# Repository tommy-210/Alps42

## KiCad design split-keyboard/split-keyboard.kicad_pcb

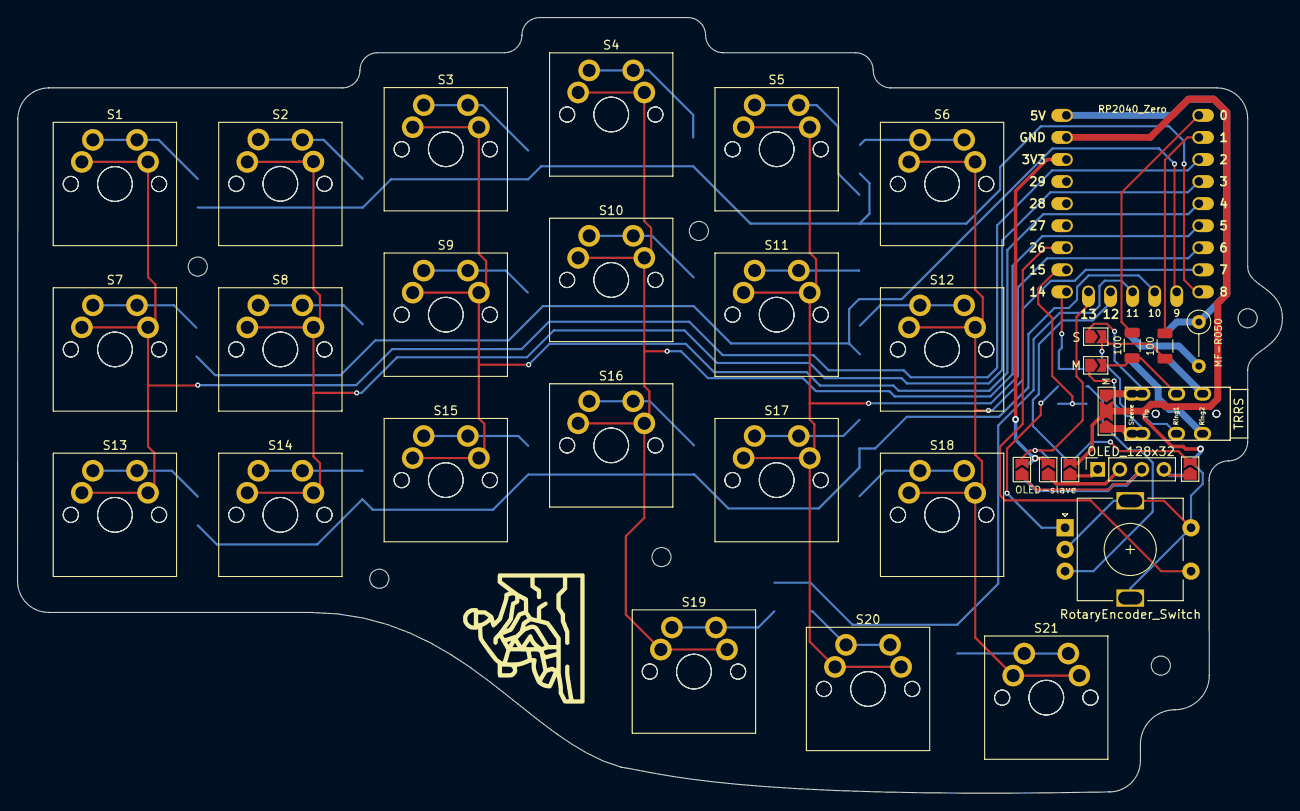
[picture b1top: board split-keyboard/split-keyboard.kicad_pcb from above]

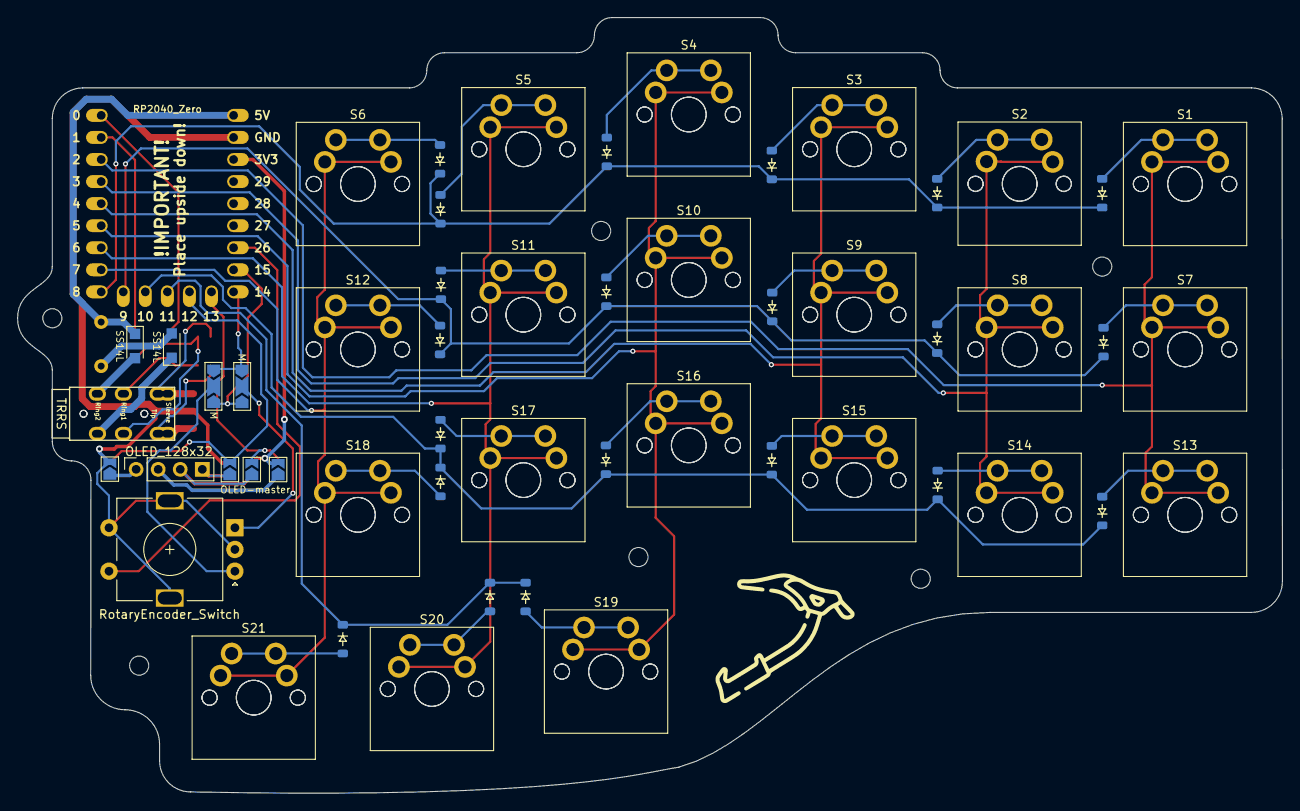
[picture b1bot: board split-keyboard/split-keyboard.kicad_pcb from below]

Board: 2 copper layers, 145.7 x 89.3 mm, 86 parts (51 on the bottom side), 56 nets.

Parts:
D1, D2, D3, D4, D5, D6, D7, D8, D9, D10, D11, D12, D13, D14, D15, D16, D17, D18, D19, D20, D21: Diode_SOD-123
D22, D23: SS14L; Nexperia_CFP3_SOD-123W
F1: MF-R050; R_Axial_DIN0207_L6.3mm_D2.5mm_P5.08mm_Vertical
J1: OLED_128x32; PinSocket_1x04_P2.54mm_Vertical
JP1, JP2, JP3: SolderJumper_3_Open; SolderJumper-3_P2.0mm_Open_TrianglePad1.0x1.5mm_NumberLabels
JP_MGND7: SolderJumper_2_Open; SolderJumper-2_P1.3mm_Open_TrianglePad1.0x1.5mm
JP_MSCL7: SolderJumper_2_Open; SolderJumper-2_P1.3mm_Open_TrianglePad1.0x1.5mm
JP_MSDA6: SolderJumper_2_Open; SolderJumper-2_P1.3mm_Open_TrianglePad1.0x1.5mm
JP_MTX5: SolderJumper_2_Open; SolderJumper-2_P1.3mm_Open_TrianglePad1.0x1.5mm
JP_MVCC8: SolderJumper_2_Open; SolderJumper-2_P1.3mm_Open_TrianglePad1.0x1.5mm
JP_SGND6: SolderJumper_2_Open; SolderJumper-2_P1.3mm_Open_TrianglePad1.0x1.5mm
JP_SRX4: SolderJumper_2_Open; SolderJumper-2_P1.3mm_Open_TrianglePad1.0x1.5mm
JP_SSCL8: SolderJumper_2_Open; SolderJumper-2_P1.3mm_Open_TrianglePad1.0x1.5mm
JP_SSDA5: SolderJumper_2_Open; SolderJumper-2_P1.3mm_Open_TrianglePad1.0x1.5mm
JP_SVCC7: SolderJumper_2_Open; SolderJumper-2_P1.3mm_Open_TrianglePad1.0x1.5mm
R1, R2: 100; R_1206_3216Metric
S1, S1#2, S2, S2#2, S3, S3#2, S4, S4#2, S5, S5#2, S6, S6#2, S7, S7#2, S8, S8#2, S9, S9#2, S10, S10#2, S11, S11#2, S12, S12#2, S13, S13#2, S14, S14#2, S15, S15#2, S16, S16#2, S17, S17#2, S18, S18#2, S19, S19#2, S20, S20#2, S21, S21#2: MX_PCB_1.00u
SW1: RotaryEncoder_Switch; RotaryEncoder_Alps_EC11E-Switch_Vertical_H20mm
U3: RP2040_Zero
U_M1: TRRS; TRRS_PJ-320A
U_S2: TRRS; TRRS_PJ-320A

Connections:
3.3V: JP_MVCC8.2 (B), JP_SVCC7.2 (B), U3.21 (3V3)
5V: D22.1 (K), F1.1, U3.23 (5V)
Column_1: S1.1, S1#2.1, S7.1, S7#2.1, S13.1, S13#2.1, U3.3 (2)
Column_2: S2.1, S2#2.1, S8.1, S8#2.1, S14.1, S14#2.1, U3.4 (3)
Column_3: S3.1, S3#2.1, S9.1, S9#2.1, S15.1, S15#2.1, U3.5 (4)
Column_4: S4.1, S4#2.1, S10.1, S10#2.1, S16.1, S16#2.1, S19.1, S19#2.1, U3.6 (5)
Column_5: S5.1, S5#2.1, S11.1, S11#2.1, S17.1, S17#2.1, S20.1, S20#2.1, U3.7 (6)
Column_6: S6.1, S6#2.1, S12.1, S12#2.1, S18.1, S18#2.1, S21.1, S21#2.1, U3.8 (7)
ENCODER_A: JP1.1 (A), JP2.3 (B), U3.15 (14)
ENCODER_B: JP1.3 (B), JP2.1 (A), U3.16 (15)
ENCODER_SW: SW1.S1, U3.17 (26)
GND: JP3.2 (C), JP_MGND7.2 (B), JP_SGND6.2 (B), SW1.C, SW1.MP, SW1.S2, U3.22 (GND)
unnamed: D1.2 (A), S1.2, S1#2.2
unnamed: D2.2 (A), S2.2, S2#2.2
unnamed: D3.2 (A), S3.2, S3#2.2
unnamed: D4.2 (A), S4.2, S4#2.2
unnamed: D5.2 (A), S5.2, S5#2.2
unnamed: D6.2 (A), S6.2, S6#2.2
unnamed: D7.2 (A), S7.2, S7#2.2
unnamed: D8.2 (A), S8.2, S8#2.2
unnamed: D9.2 (A), S9.2, S9#2.2
unnamed: D10.2 (A), S10.2, S10#2.2
unnamed: D11.2 (A), S11.2, S11#2.2
unnamed: D12.2 (A), S12.2, S12#2.2
unnamed: D13.2 (A), S13.2, S13#2.2
unnamed: D14.2 (A), S14.2, S14#2.2
unnamed: D15.2 (A), S15.2, S15#2.2
unnamed: D16.2 (A), S16.2, S16#2.2
unnamed: D17.2 (A), S17.2, S17#2.2
unnamed: D18.2 (A), S18.2, S18#2.2
unnamed: D19.2 (A), S19.2, S19#2.2
unnamed: D20.2 (A), S20.2, S20#2.2
unnamed: D21.2 (A), S21.2, S21#2.2
unnamed: D22.2 (A), U_S2.4 (RING2)
unnamed: D23.2 (A), F1.2
unnamed: D23.1 (K), U_M1.4 (RING2)
unnamed: J1.1, JP_MSDA6.1 (A), JP_SGND6.1 (A)
unnamed: J1.2, JP_MSCL7.1 (A), JP_SVCC7.1 (A)
unnamed: J1.3, JP_MVCC8.1 (A), JP_SSCL8.1 (A)
unnamed: J1.4, JP_MGND7.1 (A), JP_SSDA5.1 (A)
unnamed: JP1.2 (C), SW1.A
unnamed: JP2.2 (C), SW1.B
unnamed: JP3.1 (A), U_M1.1 (SLEEVE)
unnamed: JP3.3 (B), U_S2.1 (SLEEVE)
unnamed: JP_MTX5.1 (A), U_M1.2 (TIP)
unnamed: JP_SRX4.1 (A), U_S2.2 (TIP)
unnamed: R1.1, U3.1 (0)
unnamed: R2.1, U3.2 (1)
RX: JP_SRX4.2 (B), R2.2, U_M1.3 (RING1)
Row_1: D1.1 (K), D2.1 (K), D3.1 (K), D4.1 (K), D5.1 (K), D6.1 (K), U3.9 (8)
Row_2: D7.1 (K), D8.1 (K), D9.1 (K), D10.1 (K), D11.1 (K), D12.1 (K), U3.10 (9)
Row_3: D13.1 (K), D14.1 (K), D15.1 (K), D16.1 (K), D17.1 (K), D18.1 (K), U3.11 (10)
Row_4: D19.1 (K), D20.1 (K), D21.1 (K), U3.12 (11)
SCL: JP_MSCL7.2 (B), JP_SSCL8.2 (B), U3.14 (13)
SDA: JP_MSDA6.2 (B), JP_SSDA5.2 (B), U3.13 (12)
TX: JP_MTX5.2 (B), R1.2, U_S2.3 (RING1)

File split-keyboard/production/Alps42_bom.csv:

Designator,Footprint,Quantity,Value,LCSC Part #
"D1, D10, D11, D12, D13, D14, D15, D16, D17, D18, D19, D2, D20, D21, D3, D4, D5, D6, D7, D8, D9",Diode_SOD-123,21,~,
"D22, D23",Nexperia_CFP3_SOD-123W,2,SS14L,
F1,R_Axial_DIN0207_L6.3mm_D2.5mm_P5.08mm_Vertical,1,MF-R050,
J1,PinSocket_1x04_P2.54mm_Vertical,1,OLED_128x32,
"R1, R2",1206,2,100,
"S1_2, S1, S10_2, S10, S11_2, S11, S12_2, S12, S13_2, S13, S14_2, S14, S15_2, S15, S16_2, S16, S17_2, S17, S18_2, S18, S19_2, S19, S2_2, S2, S20_2, S20, S21_2, S21, S3_2, S3, S4_2, S4, S5_2, S5, S6_2, S6, S7_2, S7, S8_2, S8, S9_2, S9",MX_PCB_1.00u,42,~,
SW1,RotaryEncoder_Alps_EC11E-Switch_Vertical_H20mm,1,RotaryEncoder_Switch,
U3,RP2040_Zero,1,RP2040_Zero,
"U_M1, U_S2",TRRS_PJ-320A,2,TRRS,

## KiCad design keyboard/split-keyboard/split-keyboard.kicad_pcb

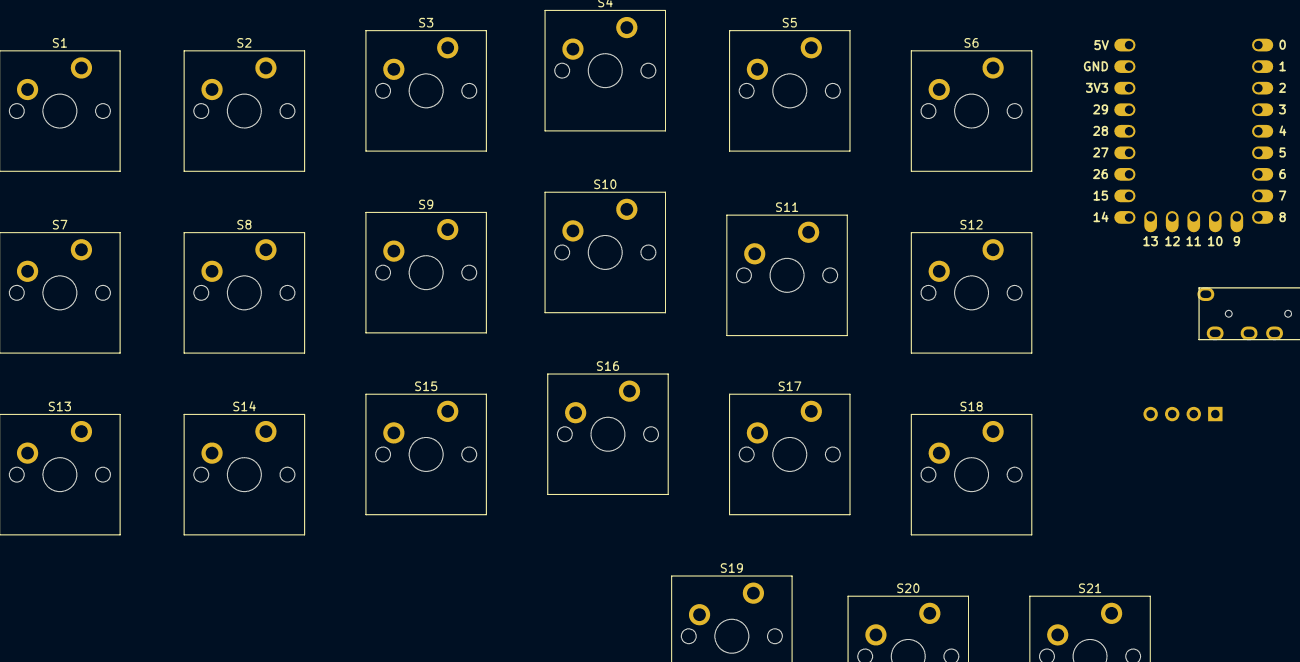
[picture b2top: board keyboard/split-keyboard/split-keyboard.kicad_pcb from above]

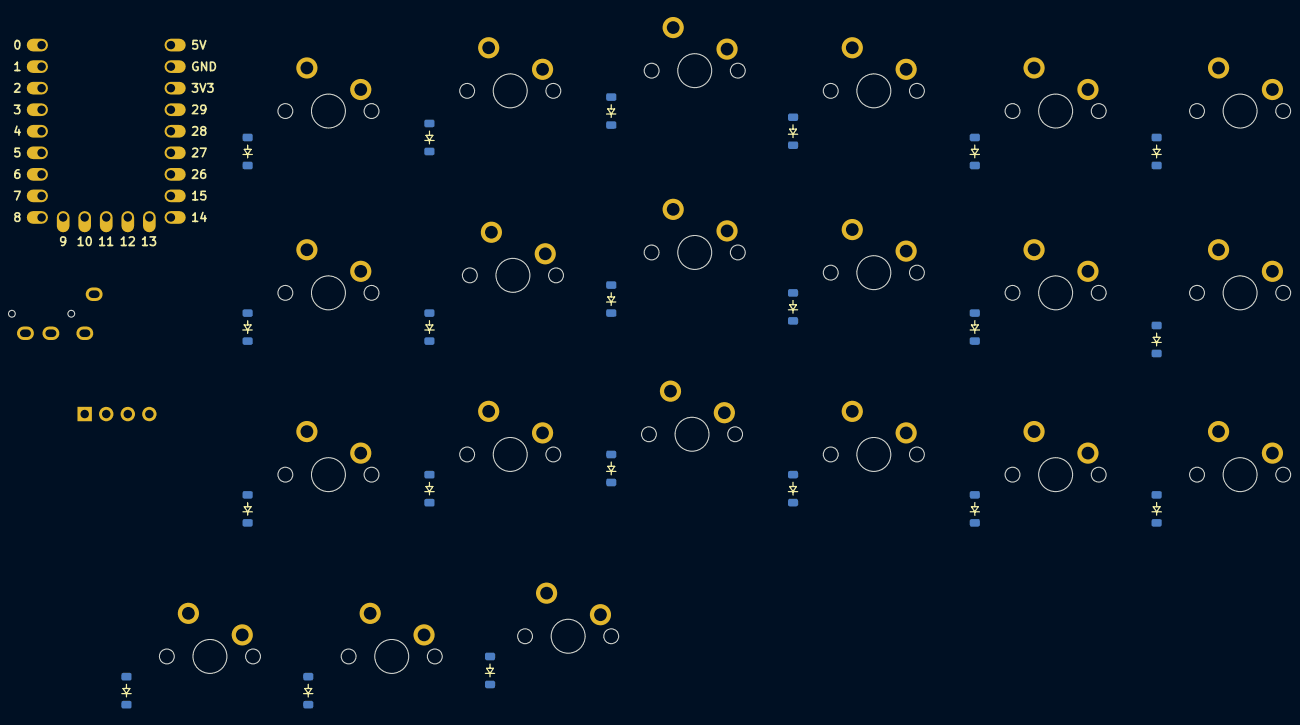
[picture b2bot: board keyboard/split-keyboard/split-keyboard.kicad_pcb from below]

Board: 2 copper layers, 45 parts (21 on the bottom side), 37 nets, no tracks yet.

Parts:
D1, D2, D3, D4, D5, D6, D7, D8, D9, D10, D11, D12, D13, D14, D15, D16, D17, D18, D19, D20, D21: Diode_SOD-123
J1: OLED_128x64; OLED_128x32
S1, S2, S3, S4, S5, S6, S7, S8, S9, S10, S11, S12, S13, S14, S15, S16, S17, S18, S19, S20, S21: MX_PCB_1.00u
U1: TRRS; TRRS_PJ-320A
U2: RP2040_Zero

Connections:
3.3V: J1.2 (VCC), U2.21 (3V3)
Column_1: S1.1, S7.1, S13.1, U2.1 (0)
Column_2: S2.1, S8.1, S14.1, U2.2 (1)
Column_3: S3.1, S9.1, S15.1, U2.3 (2)
Column_4: S4.1, S10.1, S16.1, S19.1, U2.4 (3)
Column_5: S5.1, S11.1, S17.1, S20.1, U2.5 (4)
Column_6: S6.1, S12.1, S18.1, S21.1, U2.6 (5)
GND: J1.1 (GND), U1.1 (SLEEVE), U1.3 (RING1), U2.22 (GND)
unnamed: D1.2 (A), S1.2
unnamed: D2.2 (A), S2.2
unnamed: D3.2 (A), S3.2
unnamed: D4.2 (A), S4.2
unnamed: D5.2 (A), S5.2
unnamed: D6.2 (A), S6.2
unnamed: D7.2 (A), S7.2
unnamed: D8.2 (A), S8.2
unnamed: D9.2 (A), S9.2
unnamed: D10.2 (A), S10.2
unnamed: D11.2 (A), S11.2
unnamed: D12.2 (A), S12.2
unnamed: D13.2 (A), S13.2
unnamed: D14.2 (A), S14.2
unnamed: D15.2 (A), S15.2
unnamed: D16.2 (A), S16.2
unnamed: D17.2 (A), S17.2
unnamed: D18.2 (A), S18.2
unnamed: D19.2 (A), S19.2
unnamed: D20.2 (A), S20.2
unnamed: D21.2 (A), S21.2
Row_1: D1.1 (K), D2.1 (K), D3.1 (K), D4.1 (K), D5.1 (K), D6.1 (K), U2.7 (6)
Row_2: D7.1 (K), D8.1 (K), D9.1 (K), D10.1 (K), D11.1 (K), D12.1 (K), U2.8 (7)
Row_3: D13.1 (K), D14.1 (K), D15.1 (K), D16.1 (K), D17.1 (K), D18.1 (K), U2.9 (8)
Row_4: D19.1 (K), D20.1 (K), D21.1 (K), U2.10 (9)
SCL: J1.3 (SCL), U2.14 (13)
SDA: J1.4 (SDA), U2.13 (12)
Serial_TRRS: U1.2 (TIP), U2.15 (14)
VCC: U1.4 (RING2), U2.23 (5V)
